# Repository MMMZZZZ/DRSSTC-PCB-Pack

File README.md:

I created a [new version of the UD2.7 THT](/ud27c%20thru%20hole#readme). No other changes, so here's the original readme:

Dual Resonant Solid State Tesla Coil and Solid State Tesla Coil PCB pack.
Copyright (C) 2018 by Daniel L. Marks, licensed under the Created Commons CC-BY-SA 4.0.

These are PCBs for use in DRSSTC/SSTC devices.  They are projects using
the free and open source Kicad software (kicad-pcb.org) version 4.0.7, so these projects
may be modified using this software.  Each file includes the following:

1.  Kicad project, so it can be modified or improved
2.  PDF Schematic
3.  Bill of materials, to refer to when assembling
4.  PNG circuit board picture, to refer to when assembling
5.  Gerber files

The projects, except for the interrupters, are 100 by 100 mm boards with 90 by 90 mm
mounting hole spacing.  These boards may be stacked using M3 spacers. Board of this 
size can often be fabricated for $5 (without shipping) from PCB manufacturers such as
Seeedstudio.  You can save on shipping per board if you have several of
these made at a time, for example, the driver, interrupter, and a bridge board.  

The projects are as follows:

ud27c - a through hole version of the Universal Tesla coil driver, version 2.7C.
          This is based on a design originally by Steve Ward and refined by others including
          Eric Goodchild and Gao Guangyan.  It has substituted the through-hole parts 
          IRF540N/IRF9540N complementary MOSFET pair for the FDD8424H dual MOSFET part.
          It includes phase lead, unlike the Universal Driver v1.3.

ud29 - an experimental version of ud27c that includes skip pulse functionality.  Pulse skip is
          enabled or disabled using a jumper, so it may be used as a normal DRSSTC controller.
		  The board has been built and worked for my coil.
		  
PSoc5-power - a through-hole version of the Universal Driver 3 by Steve Ward and Jens Kerrinnes
          based on the PSoC5 system-on-chip. This includes the functionality for temperature,
		  bus voltage, and bus current sensing.	 This is experimental.  It uses the CYC8KIT-059
		  dev board plugged into the PCB using pin header sockets.

interrupter - a DRSSTC interrupter based on Steve Ward's burst mode interrupter.  It
          includes a place for the IFE97 LED optical fiber transmission unit.  The ability
          to include an external pulse trigger signal has been included for use with audio
          sources.  Also includes a spot on the board for a OneTesla 
		  ATTINY85-based MIDI interrupter which may be flashed with the OneTesla code through
		  the ICSP interface.

lineinterrupter - an experimental interrupter that interrupts on the peak of the AC cycle.
           Interrupting only at the peak of the AC cycle is intended to improve the power factor
		   by minimizing the inrush of current into the bus capacitors as the magnitude of
		   the voltage increases.  
		  
NOTE: You need to flash the included firmware on your ATTINY85 for the MIDI interrupter to work.
Instructions are in the folder "oneTesla-usbInterrupter-software".
		  
half-bridge-sstc - a half-bridge/full-bridge driver designed by myself
          that can either self-oscillate, or take an extetrnal antenna input from a
          Solid State Tesla Coil.  It includes overcurrent and undervoltage protection.
	  
half-bridge-transistor - a layout for a two TO-247 transistor half-bridge that includes
          an area for the capacitor divider network.  Note the polarity on the gates indicated
          on the silkscreening always indicates the negative and positive voltage side of
          the gate; wire the phases of the gates accordingly (oppositely in this case).  This
          convention is followed for all of the layouts.  Space is included for both
          supply bypass/DC Link capacitors and snubber capacitors.
	  
full-bridge-transistor - a layout for a four TO-247 transistor full-bridge.  Space is included
          for supply bypass DC/Link capacitors and snubber capacitors.  The two high-side gates
          should have their polarities wired oppositely, the two low-side gates should
          have their polarities wired oppositely, and the high and low-side gates of each half-bridge
          should be have their polarities wired oppositely.
	  
half-bridge-multi - a layout for an eight TO-247 transistor half-bridge, with four transistors
          of each side of the half-bridge.  The transistors should have a positive temperature
          coefficient to share current more equally.  The high and low-side gates should have their
          polarities wired oppositely.
	  
full-bridge-multi - a layout for an eight TO-247 transistor full-bridge, with two transistors on
          each side of each half bridge.  The two high-side gates should have their 
          polarities wired oppositely, the two low-side gates should have their polarities
          wired oppositely, and the high and low-side gates of each half-bridge
	      should be have their polarities wired oppositely.

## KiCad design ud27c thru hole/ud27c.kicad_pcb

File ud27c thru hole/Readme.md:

# UD2.7 Through Hole

## Description

This folder contains the KiCad files for the through hole edition of the UD2.7 DRSSTC driver. It uses the schematic and the footprints from the original UD2.7 THT profdc9 made. However, the layout is completely new.

Features:

* PCB can be manufactured as standard double sided PCB *and* as **single sided**. 
	* Top layer only contains straight connections that can be replaced by jumper wires. Note that this assumes you're using sockets for the ICs.
	* No layout modifications needed for single or double side manufacturing. 
	* Single side should be easier to manufacture at home. 
* All TO220 parts are on the same side of the PCB. One common (isolated!) heatsink can be used.
* Optical inputs and status LEDs are on the opposite side of the heatsink. All inputs are grouped on the left side, the GDT output is on the right.
* All testpoints are on the edge of the PCB. 
* All terminals, jumpers and tespoints are labeled. DC In and testpoints have the pinout marked as well.
* PCB size: 99mm x 99mm
* [Interactive BOM](http://htmlpreview.github.io/?https://github.com/MMMZZZZ/DRSSTC-PCB-Pack/blob/master/ud27c%20thru%20hole/bom/ud27c%20Interactive%20BOM.html). An HTML document that allows you to visualize what part sits where. Great help during assembly! It allows highlighting nets, too, which is very useful for debugging. If you want to use it offline, right click and save as on the following link: [Interactive BOM, raw file](https://github.com/MMMZZZZ/DRSSTC-PCB-Pack/raw/master/ud27c%20thru%20hole/bom/ud27c%20Interactive%20BOM.html).

## Preview

Here are some pics. Since the layout was made with single side manufacturing in mind, the routing doesn't look that clean but it should work. Power and ground are somewhat star like.

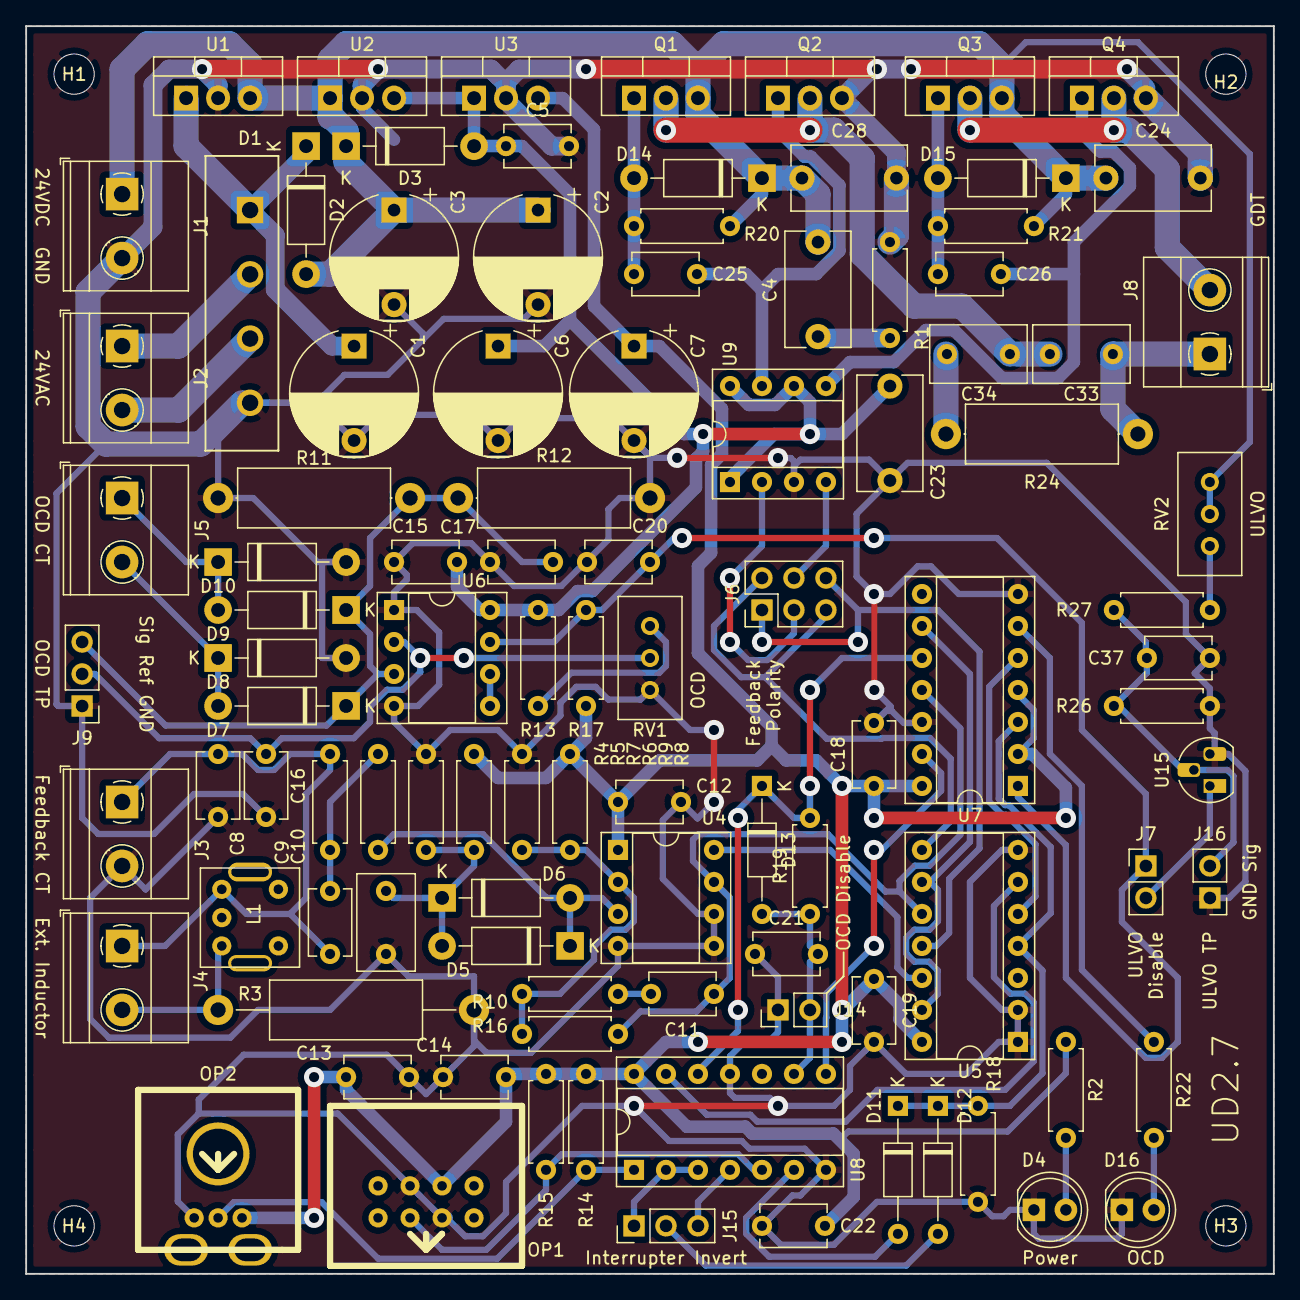
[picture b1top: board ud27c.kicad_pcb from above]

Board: 2 copper layers, 99.1 x 99.1 mm, 106 parts (0 on the bottom side), 55 nets.

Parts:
C1, C2, C3: 100 uF; CP_Radial_D10.0mm_P7.50mm
C4, C24, C28: 4.7 uF; C_Disc_D9.0mm_W5.0mm_P7.50mm
C5, C9, C12, C13, C14, C15, C16, C18, C19, C22, C25, C26: 0.1 uF; C_Disc_D5.1mm_W3.2mm_P5.00mm
C6, C7: 330 uF; CP_Radial_D10.0mm_P7.50mm
C8: 150 pF; C_Disc_D5.1mm_W3.2mm_P5.00mm
C10, C34: 1 uF; C_Disc_D7.5mm_W4.4mm_P5.00mm
C11, C17, C20, C37: 1 nF; C_Disc_D5.1mm_W3.2mm_P5.00mm
C21: 10 nF; C_Disc_D5.1mm_W3.2mm_P5.00mm
C23: 1.0 uF; C_Disc_D9.0mm_W5.0mm_P7.50mm
C33: 2.2 uF; C_Disc_D7.5mm_W4.4mm_P5.00mm
D1: D_Bridge_-AA+; Diode_Bridge_18.5x5.5_4321
D2, D3: 1N4007; D_DO-41_SOD81_P10.16mm_Horizontal
D4: PWR-LED; LED_D5.0mm
D5, D6, D7, D8, D9, D10: 1N5818; D_DO-41_SOD81_P10.16mm_Horizontal
D11, D12, D13: 1N4148; D_DO-35_SOD27_P10.16mm_Horizontal
D14, D15: 1N4148; D_DO-41_SOD81_P10.16mm_Horizontal
D16: OCD-LED; LED_D5.0mm
H1, H2, H3, H4: MountingHole_Pad; MountingHole_3.2mm_M3
J1: +24V-; TerminalBlock_Phoenix_MKDS-1,5-2-5.08_1x02_P5.08mm_Horizont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
J2: 24VAC; TerminalBlock_Phoenix_MKDS-1,5-2-5.08_1x02_P5.08mm_Horizont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
J3: FB-CT; TerminalBlock_Phoenix_MKDS-1,5-2-5.08_1x02_P5.08mm_Horizont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
J4: FB-IND; TerminalBlock_Phoenix_MKDS-1,5-2-5.08_1x02_P5.08mm_Horizont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
J5: OCD-CT; TerminalBlock_Phoenix_MKDS-1,5-2-5.08_1x02_P5.08mm_Horizont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
J6: FB-POLARITY; PinHeader_2x03_P2.54mm_Vertical
J7: UV-DIS; PinHeader_1x02_P2.54mm_Vertical
J8: GDT; TerminalBlock_Phoenix_MKDS-1,5-2-5.08_1x02_P5.08mm_Horizont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
J9: OCD-TP; PinHeader_1x03_P2.54mm_Vertical
J14: OCD-DIS; PinHeader_1x02_P2.54mm_Vertical
J15: INT-POLARITY; PinHeader_1x03_P2.54mm_Vertical
J16: UV-TP; PinHeader_1x02_P2.54mm_Vertical
L1: SLOT7; CoilCraft_Slot_7
OP1: OPF2412T
OP2: IFD95
Q1, Q3: IRF9540N; TO-220-3_Vertical
Q2, Q4: IRF540N; TO-220-3_Vertical
R1: 1R; R_Axial_DIN0207_L6.3mm_D2.5mm_P7.62mm_Horizontal
R2, R7, R9, R10, R22, R26: 470R; R_Axial_DIN0207_L6.3mm_D2.5mm_P7.62mm_Horizontal
R3: 51R; R_Axial_DIN0414_L11.9mm_D4.5mm_P20.32mm_Horizontal
R4, R16: 100k; R_Axial_DIN0207_L6.3mm_D2.5mm_P7.62mm_Horizontal
R5, R6, R8, R14, R15, R17, R18, R20, R21, R27: 1k; R_Axial_DIN0207_L6.3mm_D2.5mm_P7.62mm_Horizontal
R11, R12: 5.1R; R_Axial_DIN0414_L11.9mm_D4.5mm_P15.24mm_Horizontal
R13: 1.8k; R_Axial_DIN0207_L6.3mm_D2.5mm_P7.62mm_Horizontal
R19: 10k; R_Axial_DIN0207_L6.3mm_D2.5mm_P7.62mm_Horizontal
R24: 15R; R_Axial_DIN0414_L11.9mm_D4.5mm_P15.24mm_Horizontal
RV1: 10k; Potentiometer_Bourns_3296W_Vertical
RV2: 5k; Potentiometer_Bourns_3296W_Vertical
U1: LM7824_TO220; TO-220-3_Vertical
U2: LM7812_TO220; TO-220-3_Vertical
U3: LM7805_TO220; TO-220-3_Vertical
U4: TL3116; DIP-8_W7.62mm_Socket
U5: 74HC08; DIP-14_W7.62mm_Socket
U6: LM311; DIP-8_W7.62mm_Socket
U7: 74HC74; DIP-14_W7.62mm_Socket
U8: 74HC14; DIP-14_W7.62mm_Socket
U9: UCC27243; DIP-8_W7.62mm_Socket
U15: MC34164; TO-92L_HandSolder

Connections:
+5V: C7.1, C12.1, C13.1, C14.1, C18.1, C19.1, C22.2, OP1.2, OP2.3, R2.1, R6.1, R8.1, R14.2, R15.1, R17.2, U3.3, U4.1, U5.14, U7.2, U7.4, U7.14, U8.14
+12V: C5.1, C6.1, C15.2, C23.2, D3.2, R13.1, U2.3, U3.1, U6.8, U9.1, U9.6, U9.8
+24V: C2.1, C3.1, C4.1, C24.1, C28.1, D2.2, D3.1, D14.1, D15.1, J1.1, Q1.3, Q3.3, R20.1, R21.1, RV2.2, RV2.3, U1.3, U2.1
GND: C1.2, C2.2, C3.2, C5.2, C6.2, C7.2, C8.2, C10.1, C12.2, C13.2, C14.2, C15.1, C16.1, C17.2, C18.2, C19.2, C20.1, C21.1, C22.1, C23.1, C24.2, C28.2, C37.1, D1.1, D4.1, D8.2, D10.2, D16.1, H1.1, H2.1, H3.1, H4.1, J1.2, J3.2, J9.1, J14.1, J16.1, OP1.3, OP1.7, OP2.1, Q2.3, Q4.3, R1.2, R3.2, R7.2, R9.2, R11.2, R12.2, R18.1, R26.2, RV1.3, U1.2, U2.2, U3.2, U4.4, U4.5, U4.6, U5.1, U5.2, U5.7, U6.1, U6.4, U7.7, U7.12, U8.7, U8.11, U9.3, U15.3
unnamed: C1.1, D1.4, D2.1, U1.1
unnamed: C4.2, R1.1
unnamed: C8.1, C9.2, J3.1, J4.1, L1.3, R4.2
unnamed: C9.1, R4.1, R5.2
unnamed: C10.2, D5.2, D6.1, R6.2, R7.1
unnamed: C11.1, R16.2, U4.7, U5.10, U7.11
unnamed: C11.2, R10.2
unnamed: C16.2, J9.2, RV1.2, U6.2
unnamed: C17.1, D7.1, D9.1, J9.3, R11.1, R12.1, U6.3
unnamed: C20.2, J7.1, R17.1, U6.7, U7.1
unnamed: C21.2, D13.2, J14.2, R19.1, U8.9
unnamed: C25.1, D14.2, Q1.1, R20.2
unnamed: C25.2, Q2.1, U9.7
unnamed: C26.1, D15.2, Q3.1, R21.2
unnamed: C26.2, Q4.1, U9.5
unnamed: C33.1, C34.1, Q1.2, Q2.2
unnamed: C33.2, J8.1, R24.2
unnamed: C34.2, R24.1
unnamed: C37.2, J16.2, R26.1, R27.2, U15.2
unnamed: D1.2, J2.2
unnamed: D1.3, J2.1
unnamed: D4.2, R2.2
unnamed: D5.1, D6.2, R5.1, U4.3
unnamed: D7.2, D8.1, J5.2
unnamed: D9.2, D10.1, J5.1
unnamed: D11.1, D12.1, R18.2, U5.4, U7.3
unnamed: D11.2, U8.6
unnamed: D12.2, J15.2
unnamed: D13.1, R19.2, U7.10, U8.12
unnamed: D16.2, R22.2
unnamed: J4.2, L1.1, R3.1
unnamed: J6.1, J6.6, U5.11
unnamed: J6.2, J6.5, U5.8
unnamed: J6.3, U9.2
unnamed: J6.4, U9.4
unnamed: J7.2, U15.1
unnamed: J8.2, Q3.2, Q4.2
unnamed: J15.1, U8.2, U8.3
unnamed: J15.3, U8.4
unnamed: OP1.6, R15.2, U8.5
unnamed: OP2.2, R14.1, U8.1
unnamed: R8.2, R9.1, R10.1, R16.1, U4.2
unnamed: R13.2, RV1.1
unnamed: R22.1, U7.6
unnamed: R27.1, RV2.1
unnamed: U4.8, U5.12
unnamed: U5.5, U7.5
unnamed: U5.6, U8.13
unnamed: U5.9, U5.13, U7.9
unnamed: U6.5, U6.6
unnamed: U7.13, U8.8

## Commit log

2021-03-01 Migrated to v5.1.9 (only as far as necessary), started layout
    A lot of schematic symbols that are part of the standard library (like +24V) are taken from the rescure library and should be changed to the standard ones. Todo for a future, bored version of me.
2021-03-02 Done
2021-03-02 Readme
2021-03-02 Interactive BOM
2021-03-02 Trying to fix BOM Link
2021-03-02 iBOM Preview and Download
2021-03-03 Optimizations
